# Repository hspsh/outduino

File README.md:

# Outduino

This is a board we did back in 2023, for our ninja warrior timer.

The core requirements of the projects were - create a device that would:
* drive 2 HDMI outputs (for timer output)
* Register inputs from large switches, on very long cables
* Flash LED outputs.

At first we considered adding some I/O buffer circuitry to raspberry pi, but we decided that a cheaper and more reliable version (if not the more interesting one!) would consist of a Dell Wyse 3040 hidden inside a case, and having a standalone, overengineered, ESP-based IO module drive and read Inputs/Outputs. This is how Outduino was made.

## I/O block

The device contains 4 overengineered blocks of I/O. These should be able to handle very long cables, as long as the peripherals are not going across different electrical phases. This installation was used outdoor, so this is fine.

As I'm writing this, the year is 2026, I'm 3 years wiser, and I'd probably go full galvanic isolation for both input (optocoupler) and output (something like B0505S isolated converter).

## ESP32

The board connects via USB, and uses very simple API via serial port, to control I/O from software running on host machine.

This part worked well.

In future, the board could've been made to work wirelessly. There's even a footprint for CC1101 sub-ghz wireless IC connection. These functionalities were never added to the firmware.

## Thank yous

Thank you LiquidLemon, not7cd, for inviting me to the project.

[Project website](https://hsp.sh/chronowarrior)

## License

Copyright 2023 Jakub "cr1tbit" Sadowski.

* **Hardware** (KiCad sources, production files and this documentation) is
  licensed under the [CERN-OHL-P v2](LICENSE) (permissive). You may
  redistribute and modify it and make products using it under the terms of
  that licence.
* **Firmware** in [outduino-fw/](outduino-fw/) is licensed under the
  [MIT License](outduino-fw/LICENSE).

This source is distributed WITHOUT ANY EXPRESS OR IMPLIED WARRANTY, INCLUDING
OF MERCHANTABILITY, SATISFACTORY QUALITY AND FITNESS FOR A PARTICULAR PURPOSE.
Please see the CERN-OHL-P v2 for applicable conditions.

Symbols and footprints from the KiCad and Espressif libraries embedded in the
design files remain under their respective licences.

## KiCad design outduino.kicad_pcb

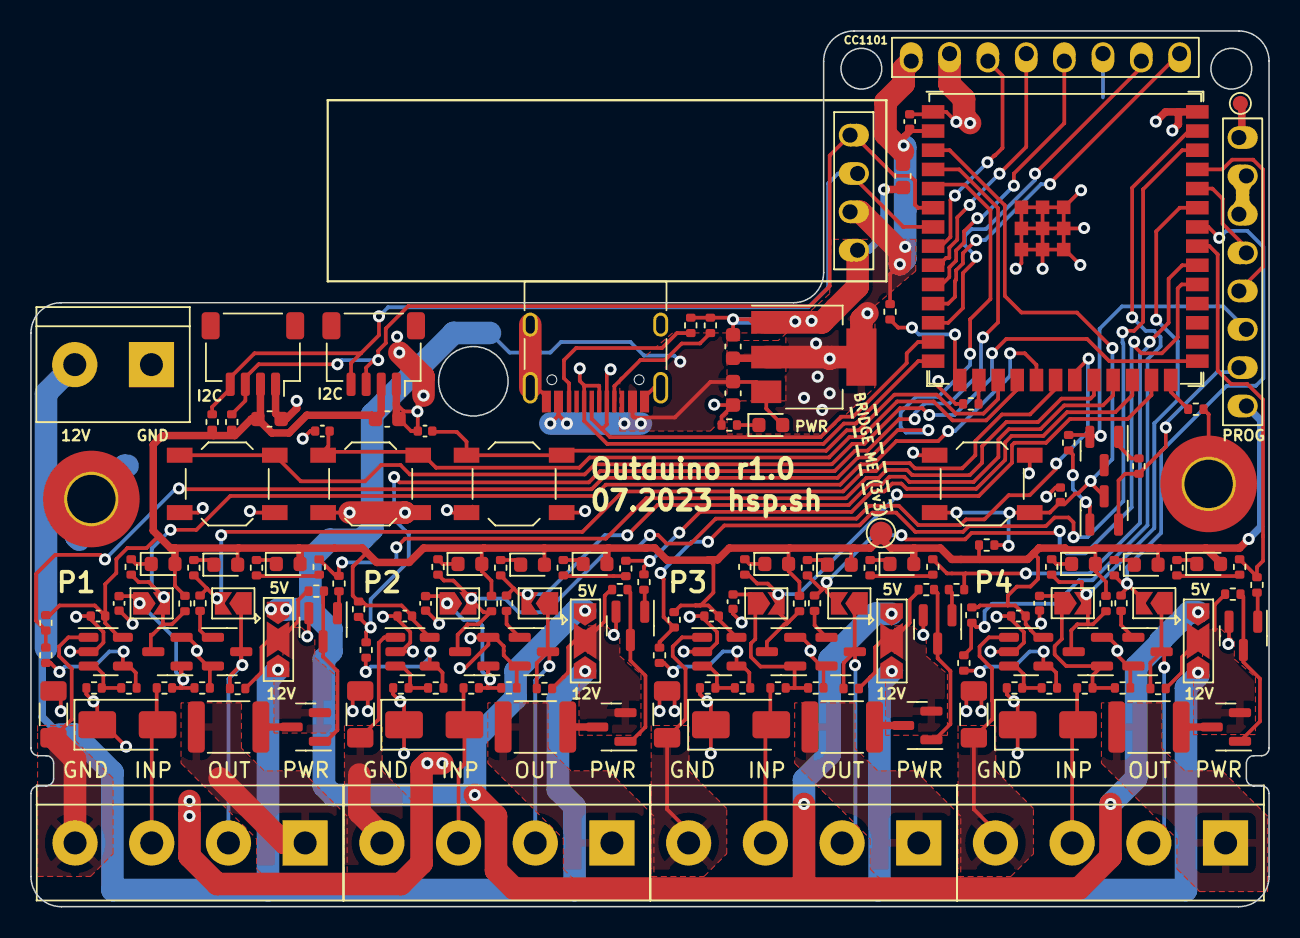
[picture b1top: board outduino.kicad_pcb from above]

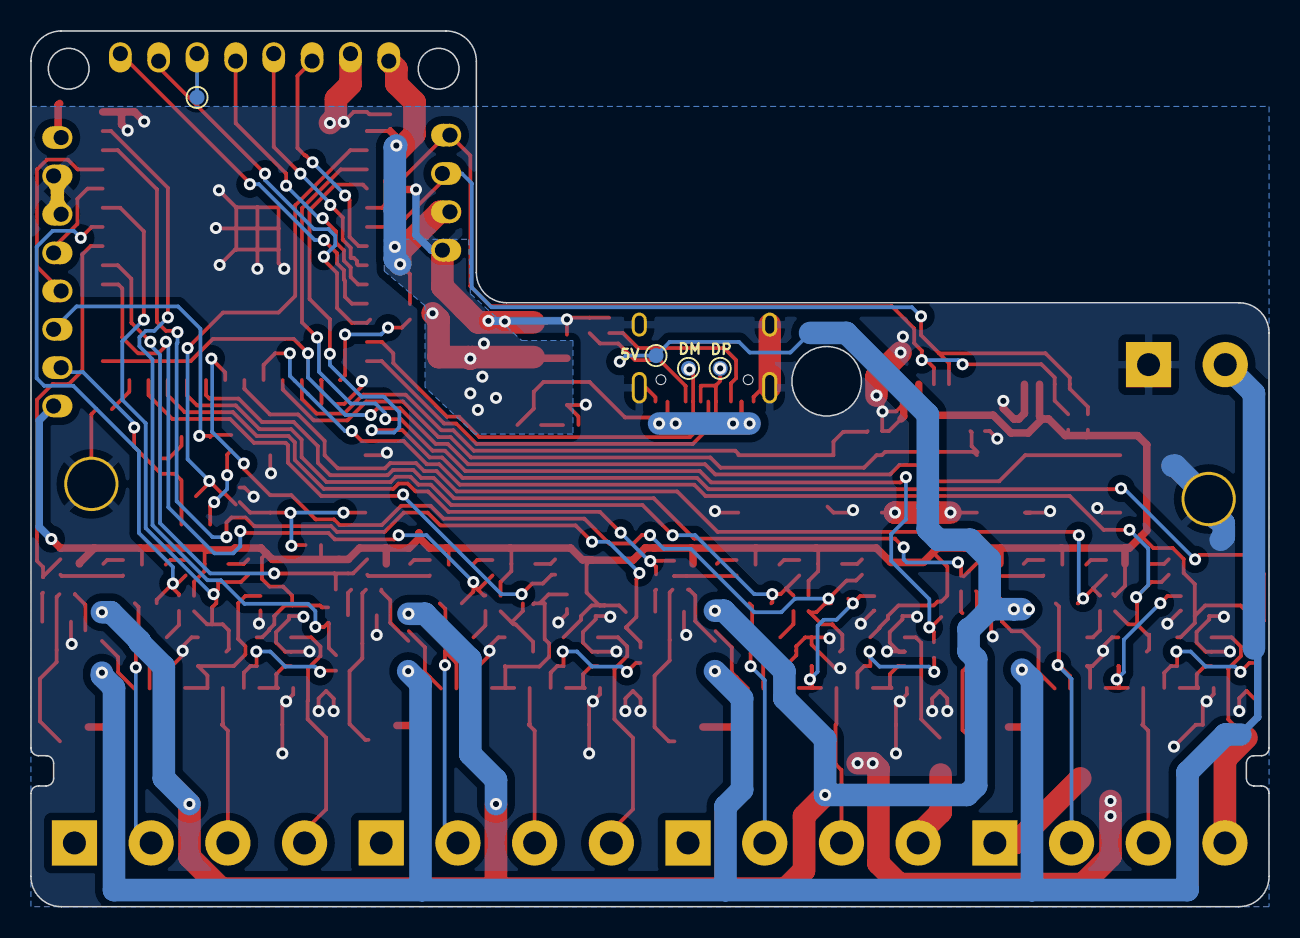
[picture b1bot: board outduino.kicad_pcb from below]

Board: 2 copper layers, 82.0 x 58.0 mm, 172 parts (4 on the bottom side), 111 nets.

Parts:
C1, C5, C6, C7, C8, C9, C10, C11, C12, C13, C14, C15: 100n; C_0402_1005Metric
C2, C3, C4, C16, C17: 10u; C_0603_1608Metric
D1, D4, D7, D12, D17: LED_RED; LED_0603_1608Metric
D3, D11, D16, D21: D_TVS; D_SMA
D5, D8, D13, D18: LED_GREEN; LED_0603_1608Metric
D6, D9, D14, D19: LED_BLUE; LED_0603_1608Metric
F1, F2, F3, F4: 1812_2A; Fuse_1812_4532Metric
H1, H3: SCR; MountingHole_3.2mm_M3_Pad_TopOnly
J1: USB_C_Receptacle_USB2.0; USB_C_Receptacle_HRO_TYPE-C-31-M-12
J2: Lichtenprog_conn; Lichtenprog
J3: Conn_01x02; TerminalBlock_bornier-2_P5.08mm
J4, J6: QWIIC; JST_SH_SM04B-SRSS-TB_1x04-1MP_P1.00mm_Horizontal
J5, J7, J8, J9: Conn_01x04; TerminalBlock_bornier-4_P5.08mm
J10: CC1101_CONN; 8pin_skewed
JP3, JP4, JP5, JP6: VSEL; SolderJumper-3_P2.0mm_Open_TrianglePad1.0x1.5mm
JP7, JP8, JP9, JP10: OUT_BYP; SolderJumper-2_P1.3mm_Open_TrianglePad1.0x1.5mm
JP11, JP12, JP13, JP14: IN_BYP; SolderJumper-2_P1.3mm_Open_TrianglePad1.0x1.5mm
Q1, Q2: MMBT2222A; SOT-23
Q3, Q6, Q9, Q12: AO3401A; SOT-23
Q4, Q5, Q7, Q8, Q10, Q11, Q13, Q14, Q15, Q16, Q17, Q18: BC847; SOT-23
R1, R7, R8, R9, R10, R11, R12, R13, R14, R19, R21, R22, R23, R24, R25, R26, R27, R28, R33, R39, R40, R41, R42, R43, R45, R49, R51, R52, R53, R54, R55, R57, R58, R60, R61, R63, R68, R69, R70, R71, R72, R73, R74, R75: 10k; R_0402_1005Metric
R2, R3: 5.1k; R_0402_1005Metric
R4, R5, R15, R16, R18, R32, R35, R38, R44, R47, R50, R56, R59, R62: 3k; R_0402_1005Metric
R6, R17, R20, R34: 50mR/1206; R_1206_3216Metric_Pad1.30x1.75mm_HandSolder
R29, R30, R31: 100k; R_0402_1005Metric
R36, R37, R46, R48: 330/0.1%; R_0402_1005Metric
R64, R65, R66, R67: 1k; R_0402_1005Metric
SW1: RST; SW_SPST_TL3342
SW3: B1/BOOT; SW_SPST_TL3342
SW4, SW5: B2; SW_SPST_TL3342
TP1, TP2, TP3, TP4, TP5: IOPAD; TestPoint_Pad_D1.0mm
TP6: IOPAD; TestPoint_Pad_D1.5mm
U1: OLED_4Pin
U2: AZ1117-3.3; SOT-223-3_TabPin2
U3: ESP32-S3-WROOM-2; ESP32-S3-WROOM-1U
U4, U5, U6, U7: LMV321; SOT-23-5

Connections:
+3.3V: C1.1, C2.1, C4.1, C10.1, C13.1, C14.1, C15.1, C16.1, C17.1, D4.2 (A), D5.2 (A), D6.2 (A), D7.2 (A), D8.2 (A), D9.2 (A), D12.2 (A), D13.2 (A), D14.2 (A), D17.2 (A), D18.2 (A), D19.2 (A), J2.1 (VDD), J4.2, J6.2, J10.1, R4.2, R5.2, R16.2, R25.2, R30.2, R35.2, R47.2, R59.2, R68.1, R69.1, R70.1, R71.1, TP6.1, U1.2 (VCC), U2.2 (VO), U3.2 (3V3), U4.5 (V+), U5.5 (V+), U6.5 (V+), U7.5 (V+)
+12V: J3.2, JP3.3 (B), JP4.3 (B), JP5.3 (B), JP6.3 (B)
/CC1101_CSn: J10.8, U3.11 (GPIO18/U1RXD/ADC2_CH7/CLK_OUT3)
/CC1101_GDO0: J10.7, U3.12 (GPIO8/TOUCH8/ADC1_CH7/SUBSPICS1)
/CC1101_GDO2: J10.6, TP5.1
/CC1101_SCLK: J10.4, U3.9 (GPIO16/U0CTS/ADC2_CH5/XTAL_32K_NH5)
/CC1101_SI: J10.3, U3.8 (GPIO15/U0RTS/ADC2_CH4/XTAL_32K_P)
/CC1101_SO: J10.5, U3.10 (GPIO17/U1TXD/ADC2_CH6)
/CURR1: R64.1, R68.2, U3.5 (GPIO5/TOUCH5/ADC1_CH4)
/CURR2: R65.1, R69.2, U3.4 (GPIO4/TOUCH4/ADC1_CH3)
/CURR3: R66.1, R70.2, U3.38 (GPIO2/TOUCH2/ADC1_CH1)
/CURR4: R67.1, R71.2, U3.39 (GPIO1/TOUCH1/ADC1_CH0)
/DTR: J2.3 (DTR), Q2.2 (E), R7.1
/ESP_B2: C11.1, SW4.2, U3.17 (GPIO9/TOUCH9/ADC1_CH8/FSPIHD/SUBSPIHD)
/ESP_B3: C12.1, SW5.2, U3.18 (GPIO10/TOUCH10/ADC1_CH9/FSPICS0/FSPIIO4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)
/ESP_BOOT_B1: SW3.2, U3.27 (GPIO0/BOOT)
/ESP_EN: C8.1, Q1.3 (C), R25.1, SW1.2, U3.3 (EN)
/IN1: JP11.2 (B), Q5.3 (C), R16.1, R23.1, U3.19 (GPIO11/TOUCH11/ADC2_CH0/FSPID/FSPIIO5/S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)
/IN2: JP12.2 (B), Q8.3 (C), R27.1, R35.1, U3.21 (GPIO13/TOUCH13/ADC2_CH2/FSPIQ/FSPIIO7/S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)
/IN3: JP13.2 (B), Q11.3 (C), R42.1, R47.1, U3.25 (GPIO48/SPICLK_N/SUBSPICLK_N_DIFF)
/IN4: JP14.2 (B), Q14.3 (C), R54.1, R59.1, U3.35 (MTMS/GPIO42)
/IO_block1/GND_BANK: J5.4, R6.1, U4.1 (+)
/IO_block1/INP_BANK: D3.2 (A2), J5.3, R18.1
/IO_block1/OUT_BANK: J5.2, JP7.1 (A), Q4.3 (C), R15.1
/IO_block1/PWR: JP3.2 (C), Q3.2 (S), R14.2, R15.2
/IO_block1/PWR_BANK: F1.2, J5.1
/IO_block2/GND_BANK: J7.4, R17.1, U5.1 (+)
/IO_block2/INP_BANK: D11.2 (A2), J7.3, R38.1
/IO_block2/OUT_BANK: J7.2, JP8.1 (A), Q7.3 (C), R32.1
/IO_block2/PWR: JP4.2 (C), Q6.2 (S), R32.2, R33.2
/IO_block2/PWR_BANK: F2.2, J7.1
/IO_block3/GND_BANK: J8.4, R20.1, U6.1 (+)
/IO_block3/INP_BANK: D16.2 (A2), J8.3, R50.1
/IO_block3/OUT_BANK: J8.2, JP9.1 (A), Q10.3 (C), R44.1
/IO_block3/PWR: JP5.2 (C), Q9.2 (S), R44.2, R45.2
/IO_block3/PWR_BANK: F3.2, J8.1
/IO_block4/GND_BANK: J9.4, R34.1, U7.1 (+)
/IO_block4/INP_BANK: D21.2 (A2), J9.3, R62.1
/IO_block4/OUT_BANK: J9.2, JP10.1 (A), Q13.3 (C), R56.1
/IO_block4/PWR: JP6.2 (C), Q12.2 (S), R56.2, R57.2
/IO_block4/PWR_BANK: F4.2, J9.1
/OUT1: JP7.2 (B), R9.2, R22.1, U3.20 (GPIO12/TOUCH12/ADC2_CH1/FSPICLK/FSPIIO6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)
/OUT2: JP8.2 (B), R10.2, R26.1, U3.23 (GPIO21)
/OUT3: JP9.2 (B), R11.2, R41.1, U3.31 (GPIO38/FSPIWP/SUBSPIWP)
/OUT4: JP10.2 (B), R12.2, R53.1, U3.34 (MTDI/GPIO41/CLK_OUT1)
/PWR1: R24.1, R72.2, U3.22 (GPIO14/TOUCH14/ADC2_CH3/FSPIWP/FSPIDQS/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)
/PWR2: R28.1, R73.2, U3.24 (GPIO47/SPICLK_P/SUBSPICLK_P_DIFF)
/PWR3: R43.1, R74.2, U3.32 (MTCK/GPIO39/CLK_OUT3/SUBSPICS1)
/PWR4: R55.1, R75.2, U3.33 (MTDO/GPIO40/CLK_OUT2)
/RTS: J2.2 (RTS), Q1.2 (E), R8.1
/SCL: J4.4, J6.4, R4.1, U1.3 (SCL), U3.7 (GPIO7/TOUCH7/ADC1_CH6)
/SDA: J4.3, J6.3, R5.1, U1.4 (SDA), U3.6 (GPIO6/TOUCH6/ADC1_CH5)
/TARG_RX: J2.5 (PROG_TX), U3.36 (U0RXD/GPIO44/CLK_OUT2)
/TARG_TX: J2.4 (PROG_RX), U3.37 (U0TXD/GPIO43/CLK_OUT1)
/USBDM: J1.A7 (D-), J1.B7 (D-), TP3.1, U3.13 (GPIO19/U1RTS/ADC2_CH8/CLK_OUT2/USB_D-)
/USBDP: J1.A6 (D+), J1.B6 (D+), TP2.1, U3.14 (GPIO20/U1CTS/ADC2_CH9/CLK_OUT1/USB_D+)
GND: C1.2, C2.2, C3.2, C4.2, C5.2, C6.2, C7.2, C8.2, C9.2, C10.2, C11.2, C12.2, C13.2, C14.2, C15.2, C16.2, C17.2, D3.1 (A1), D11.1 (A1), D16.1 (A1), D21.1 (A1), H1.1, H3.1, J1.A1 (GND), J1.A12 (GND), J1.B1 (GND), J1.B12 (GND), J1.S1 (SHIELD), J2.6 (GND), J2.7 (GND), J3.1, J4.1, J6.1, J10.2, Q4.2 (E), Q5.2 (E), Q7.2 (E), Q8.2 (E), Q10.2 (E), Q11.2 (E), Q13.2 (E), Q14.2 (E), Q15.2 (E), Q16.2 (E), Q17.2 (E), Q18.2 (E), R2.2, R3.2, R6.2, R13.1, R17.2, R19.1, R20.2, R29.1, R31.1, R34.2, R36.2, R37.2, R39.1, R46.2, R48.2, R51.1, R63.1, SW1.1, SW3.1, SW4.1, SW5.1, U1.1 (GND), U2.1 (GND), U3.1 (GND), U3.40 (GND), U3.41 (GND), U4.2 (V-), U5.2 (V-), U6.2 (V-), U7.2 (V-)
unnamed: D1.1 (K), R13.2
unnamed: D4.1 (K), R21.2
unnamed: D5.1 (K), R22.2
unnamed: D6.1 (K), R23.2
unnamed: D7.1 (K), R1.2
unnamed: D8.1 (K), R26.2
unnamed: D9.1 (K), R27.2
unnamed: D12.1 (K), R40.2
unnamed: D13.1 (K), R41.2
unnamed: D14.1 (K), R42.2
unnamed: D17.1 (K), R52.2
unnamed: D18.1 (K), R53.2
unnamed: D19.1 (K), R54.2
unnamed: J1.A5 (CC1), R2.1
unnamed: J1.B5 (CC2), R3.1
unnamed: J2.8 (5V), TP4.1
unnamed: C5.1, JP11.1 (A), Q5.1 (B), R18.2, R19.2
unnamed: C6.1, JP12.1 (A), Q8.1 (B), R38.2, R39.2
unnamed: C7.1, JP13.1 (A), Q11.1 (B), R50.2, R51.2
unnamed: C9.1, JP14.1 (A), Q14.1 (B), R62.2, R63.2
unnamed: Q1.1 (B), R7.2
unnamed: Q2.1 (B), R8.2
unnamed: F1.1, Q3.3 (D)
unnamed: Q4.1 (B), R9.1
unnamed: F2.1, Q6.3 (D)
unnamed: Q7.1 (B), R10.1
unnamed: F3.1, Q9.3 (D)
unnamed: Q10.1 (B), R11.1
unnamed: F4.1, Q12.3 (D)
unnamed: Q12.1 (G), Q18.3 (C), R57.1
unnamed: Q13.1 (B), R12.1
unnamed: Q15.1 (B), R72.1
unnamed: Q3.1 (G), Q15.3 (C), R14.1
unnamed: Q16.1 (B), R73.1
unnamed: Q6.1 (G), Q16.3 (C), R33.1
unnamed: Q17.1 (B), R74.1
unnamed: Q9.1 (G), Q17.3 (C), R45.1
unnamed: Q18.1 (B), R75.1
unnamed: R1.1, R28.2
unnamed: R21.1, R24.2
unnamed: R40.1, R43.2
unnamed: R49.1, R64.2, U4.4
unnamed: R52.1, R55.2
unnamed: R58.1, R65.2, U5.4
unnamed: R60.1, R66.2, U6.4
unnamed: R61.1, R67.2, U7.4
unnamed: R30.1, U3.15 (GPIO3/TOUCH3/ADC1_CH2)
unnamed: R31.2, U3.26 (GPIO45)
unnamed: R29.2, U3.16 (GPIO46)
unnamed: R36.1, R49.2, U4.3 (-)
unnamed: R37.1, R58.2, U5.3 (-)
unnamed: R46.1, R60.2, U6.3 (-)
unnamed: R48.1, R61.2, U7.3 (-)
VBUS: C3.1, D1.2 (A), J1.A4 (VBUS), J1.A9 (VBUS), J1.B4 (VBUS), J1.B9 (VBUS), JP3.1 (A), JP4.1 (A), JP5.1 (A), JP6.1 (A), TP1.1, U2.3 (VI)

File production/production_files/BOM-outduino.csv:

Comment,Designator,Footprint,LCSC
1k,"R64,R65,R66,R67",R_0402_1005Metric,C11702
AO3401A,"Q12,Q3,Q6,Q9",SOT-23,C15127
100n,"C1,C10,C11,C12,C13,C14,C15,C5,C6,C7,C8,C9",C_0402_1005Metric,C1525
USB_C_Receptacle_USB2.0,J1,USB_C_Receptacle_HRO_TYPE-C-31-M-12,C165948
1812_2A,"F1,F2,F3,F4",Fuse_1812_4532Metric,C20999
LED_RED,"D1,D12,D17,D4,D7",LED_0603_1608Metric,C2286
330/0.1%,"R36,R37,R46,R48",R_0402_1005Metric,C25104
5.1k,R3,R_0402_1005Metric,C25117
100k,"R29,R30,R31",R_0402_1005Metric,C25741
10k,"R1,R10,R11,R12,R13,R14,R19,R21,R22,R23,R24,R25,R26,R27,R28,R33,R39,R40,R41,R42,R43,R45,R49,R51,R52,R53,R54,R55,R57,R58,R60,R61,R63,R68,R69,R7,R70,R71,R72,R73,R74,R75,R8,R9",R_0402_1005Metric,C25744
3k,"R15,R16,R18,R32,R35,R38,R4,R44,R47,R5,R50,R56,R59,R62",R_0402_1005Metric,C25890
5.1k,R2,R_0402_1005Metric,C25905
D_TVS,"D11,D16,D21,D3",D_SMA,C3019524
RST,"SW1,SW3,SW4,SW5",SW_SPST_TL3342,C318884
AZ1117-3.3,U2,SOT-223-3_TabPin2,C6186
LED_BLUE,"D14,D19,D6,D9",LED_0603_1608Metric,C72041
LED_GREEN,"D13,D18,D5,D8",LED_0603_1608Metric,C72043
LMV321,"U4,U5,U6,U7",SOT-23-5,C7972
MMBT2222A,"Q1,Q10,Q11,Q13,Q14,Q15,Q16,Q17,Q18,Q2,Q4,Q5,Q7,Q8",SOT-23,C8512
50mR/1206,"R17,R20,R34,R6",R_1206_3216Metric_Pad1.30x1.75mm_HandSolder,C912768
10u,"C16,C17,C2,C3,C4",C_0603_1608Metric,C96446

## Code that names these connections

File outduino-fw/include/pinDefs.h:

#pragma once

#define ESP_TX 37
#define ESP_RX 36

#define OUT1 12
#define OUT2 21
#define OUT3 38
#define OUT4 41

#define IN1 11
#define IN2 13
#define IN3 48
#define IN4 42

#define PWR1 14
#define PWR2 47
#define PWR3 39
#define PWR4 41

#define CURR1 5
#define CURR2 4
#define CURR3 2
#define CURR4 1

#define BOOT_B1 0
#define PIN_B2 9
#define PIN_B3 10


#define SDA 6
#define SCL 7

#define CC1101_SCLK 16
#define CC1101_SI 15
#define CC1101_SO 17
#define CC1101_CS 18
#define CC1101_GDO0 8

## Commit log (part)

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2023-06-11 add kicad
2023-07-16 before scripts
2023-07-22 production
2023-07-23 add firmware stub
2023-07-27 add firmware not stub
2023-07-29 fun stuff
2023-08-05 fix ISR bootloop
2023-08-07 move stuff to libraries on github, change crappy pin ISR management to less crappy, forgive C++
2023-08-28 no compile but will fix
2023-08-28 it now compile
